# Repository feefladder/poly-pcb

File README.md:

# Johnson solid lamps!

So I thought it'd be superduper cool to make lamps as like johnson solids, so here's some kicad files for that.

There's two versions for each polygon:
1. solder mask only.
2. Solder mask and edge cuts

So you can create directional lamps with soft light in the facing direction using the pcb as diffuser adn stronger light in the backfacing direction.

More will be added once a lamp is actually made

## Exporting for jlpcb

Great thanks to [FunDeckHermit's](https://github.com/FunDeckHermit/NURD-Template) pcb exporter. I've slightly modified it so I can run it from the top-level on any file.

upload zip file to jlpcb. It can be that edge cuts don't work. fix in inkscape.

## Making mask and edge cuts

mask:

1. Plot svgs. Set F.Cu, B.Cu to all layers
2. open F.Cu in inkscape
3. select all, 2x`Ctrl-Shift-G`, `Ctrl-Shift-C`, `Ctrl-Alt-C`, `Ctrl-Shift-+` `Ctrl-Shift-)`
4. There will be some specs, either:
   - have a great time with the node tool
   - `Ctrl-Shift-K` to unmerge, select desired polygons, `!` to invert selection and delete
4. save as...
5. in kicad, `Ctrl-Shift-L`, enable "place at position `0,0`

edge:

1. Plot svgs. Set F.Cu, B.Cu, Edge.Cuts to all layers
2. open F.Cu in inkscape
3. select all, 2x`Ctrl-Shift-G`, `Ctrl-Shift-C`, `Ctrl-Alt-C`, `Ctrl-Shift-+` 2x`Ctrl-Shift-)`
4. There will be specs and some tiny gaps/overlaps.
   - fixs specs as before
   - overlaps can be fixed with running `Ctrl-Shift-+`
   - tiny gaps are equally bad. These require some fun with the node tool
     1. `Shift-doubleclick` at the narrowest point to place nodes
     2. split
     3. overlapping nodes: box select one, shift-click to get the bottom, then select the other, connect with edge, then merge to one
4. save as...
5. in kicad, `Ctrl-Shift-L`, enable "place at position `0,0`

# Reflections after making 3 lamps and soldering 350+ LEDs

So yeah, I think I'll really order the next pcbs with the leds assembled

Bending the header pins with a pcb works, but the led next to the header may want a bit of lovd afterwards. I think the flexing causes microfractures or something, but in any case, the leds stop there

## overview

1. Sphenocorona - some leds not working because of flexing breaking solder joints. Somehow it makes noise?
2. Thawro - perfect! I removed-and-bypassed some leds because I thought they were broken, but turned out it was because of WLED shenanigans
3. Bilb - smooth rolling

## WLED shenanigans

So whenever you set a pattern at boot, the length of the strip is saved in the json at "stop", so whenever increasing strip length, the leds after will not show.

Still not sure which is the best pattern for debugging leds. Solid deffo not, it needs to be changing, because a led that got a "be pink" signal will stay pink without further input. Android is fine, but when the strip setting is much larger, it is not happy. Ideally it'd be some sort of "two-color-twinkle" or something.

## howto header pins

general policy: Every bare edge exposes headers. Use a triangle full pcb to bend them in place. You want to bend it so the pcb can be flatter than it needs to be, otherwise angled pins make inserting a headache (especially for later boards).

## sharp angles

Sharp dihedral angles make the corner leds collide, resulting in a slightly sad shape. maybe add tiny jumper pads to easily bypass a led.

## Control board

Ah yes, so the ESP32-C3-WROOM boards start up in a boot loop. To solve, you have to hold BOOT (GPIO9, next to GND) low and tap EN, as this person on Github said. GPIO9 can be set as "cycle presets" or something, because getting your phone out all the time is sad.

## Double-size?

So these lamps are like nice for in a bedroom or toilet, but for living room, make double-size pcbs with two connections so they are also compatible with the others

## blrubs

ah yes ws2812s dont like fighting data, so need to cut some data pins to avoid that.

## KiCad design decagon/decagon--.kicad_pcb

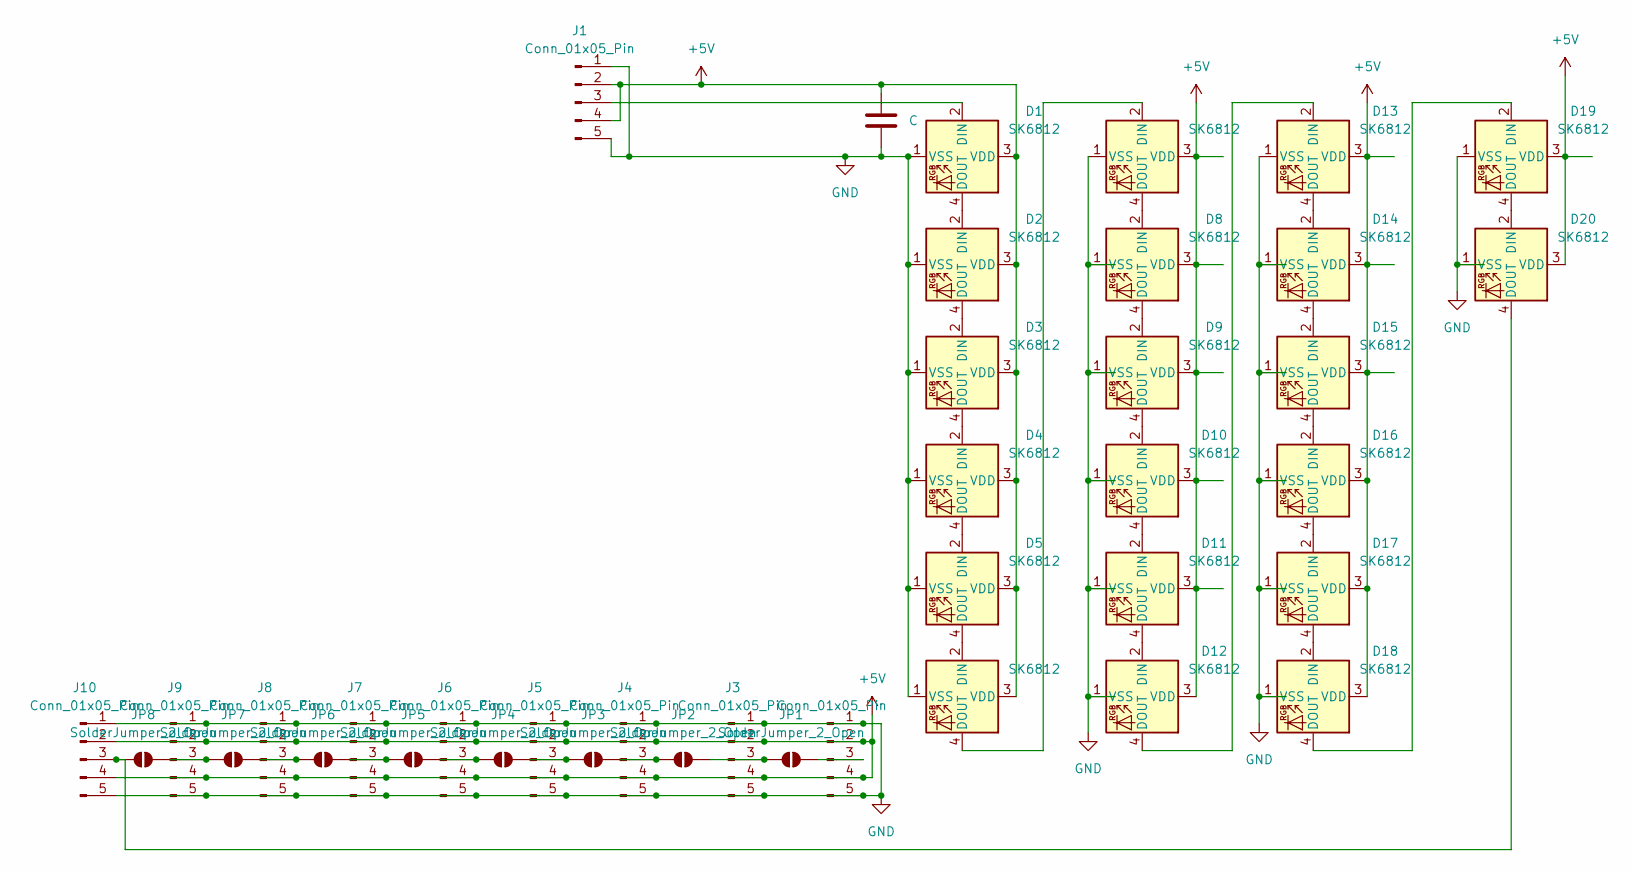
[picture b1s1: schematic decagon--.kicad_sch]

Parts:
C1: C; C_0805_2012Metric_Pad1.18x1.45mm_HandSolder
D1, D2, D3, D4, D5, D6, D7, D8, D9, D10, D11, D12, D13, D14, D15, D16, D17, D18, D19, D20: SK6812; LED_SK6812_PLCC4_5.0x5.0mm_P3.2mm
J1, J2, J3, J4, J5, J6, J7, J8, J9, J10: Conn_01x05_Pin; PinHeader_1x05_P2.54mm_Vertical
JP1, JP2, JP3, JP4, JP5, JP6, JP7, JP8: SolderJumper_2_Open; SolderJumper-2_P1.3mm_Open_RoundedPad1.0x1.5mm

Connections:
+5V: C1.2, D1.3 (VDD), D2.3 (VDD), D3.3 (VDD), D4.3 (VDD), D5.3 (VDD), D6.3 (VDD), D7.3 (VDD), D8.3 (VDD), D9.3 (VDD), D10.3 (VDD), D11.3 (VDD), D12.3 (VDD), D13.3 (VDD), D14.3 (VDD), D15.3 (VDD), D16.3 (VDD), D17.3 (VDD), D18.3 (VDD), D19.3 (VDD), D20.3 (VDD), J1.2, J1.4, J2.2, J2.4, J3.2, J3.4, J4.2, J4.4, J5.2, J5.4, J6.2, J6.4, J7.2, J7.4, J8.2, J8.4, J9.2, J9.4, J10.2, J10.4
GND: C1.1, D1.1 (VSS), D2.1 (VSS), D3.1 (VSS), D4.1 (VSS), D5.1 (VSS), D6.1 (VSS), D7.1 (VSS), D8.1 (VSS), D9.1 (VSS), D10.1 (VSS), D11.1 (VSS), D12.1 (VSS), D13.1 (VSS), D14.1 (VSS), D15.1 (VSS), D16.1 (VSS), D17.1 (VSS), D18.1 (VSS), D19.1 (VSS), D20.1 (VSS), J1.1, J1.5, J2.1, J2.5, J3.1, J3.5, J4.1, J4.5, J5.1, J5.5, J6.1, J6.5, J7.1, J7.5, J8.1, J8.5, J9.1, J9.5, J10.1, J10.5
unnamed: D1.2 (DIN), J1.3
unnamed: D1.4 (DOUT), D2.2 (DIN)
unnamed: D2.4 (DOUT), D3.2 (DIN)
unnamed: D3.4 (DOUT), D4.2 (DIN)
unnamed: D4.4 (DOUT), D5.2 (DIN)
unnamed: D5.4 (DOUT), D6.2 (DIN)
unnamed: D6.4 (DOUT), D7.2 (DIN)
unnamed: D7.4 (DOUT), D8.2 (DIN)
unnamed: D8.4 (DOUT), D9.2 (DIN)
unnamed: D9.4 (DOUT), D10.2 (DIN)
unnamed: D10.4 (DOUT), D11.2 (DIN)
unnamed: D11.4 (DOUT), D12.2 (DIN)
unnamed: D12.4 (DOUT), D13.2 (DIN)
unnamed: D13.4 (DOUT), D14.2 (DIN)
unnamed: D14.4 (DOUT), D15.2 (DIN)
unnamed: D15.4 (DOUT), D16.2 (DIN)
unnamed: D16.4 (DOUT), D17.2 (DIN)
unnamed: D17.4 (DOUT), D18.2 (DIN)
unnamed: D18.4 (DOUT), D19.2 (DIN)
unnamed: D19.4 (DOUT), D20.2 (DIN)
unnamed: D20.4 (DOUT), J10.3, JP8.1 (A)
unnamed: J2.3, JP1.2 (B)
unnamed: J3.3, JP1.1 (A), JP2.2 (B)
unnamed: J4.3, JP2.1 (A), JP3.2 (B)
unnamed: J5.3, JP3.1 (A), JP4.2 (B)
unnamed: J6.3, JP4.1 (A), JP5.2 (B)
unnamed: J7.3, JP5.1 (A), JP6.2 (B)
unnamed: J8.3, JP6.1 (A), JP7.2 (B)
unnamed: J9.3, JP7.1 (A), JP8.2 (B)

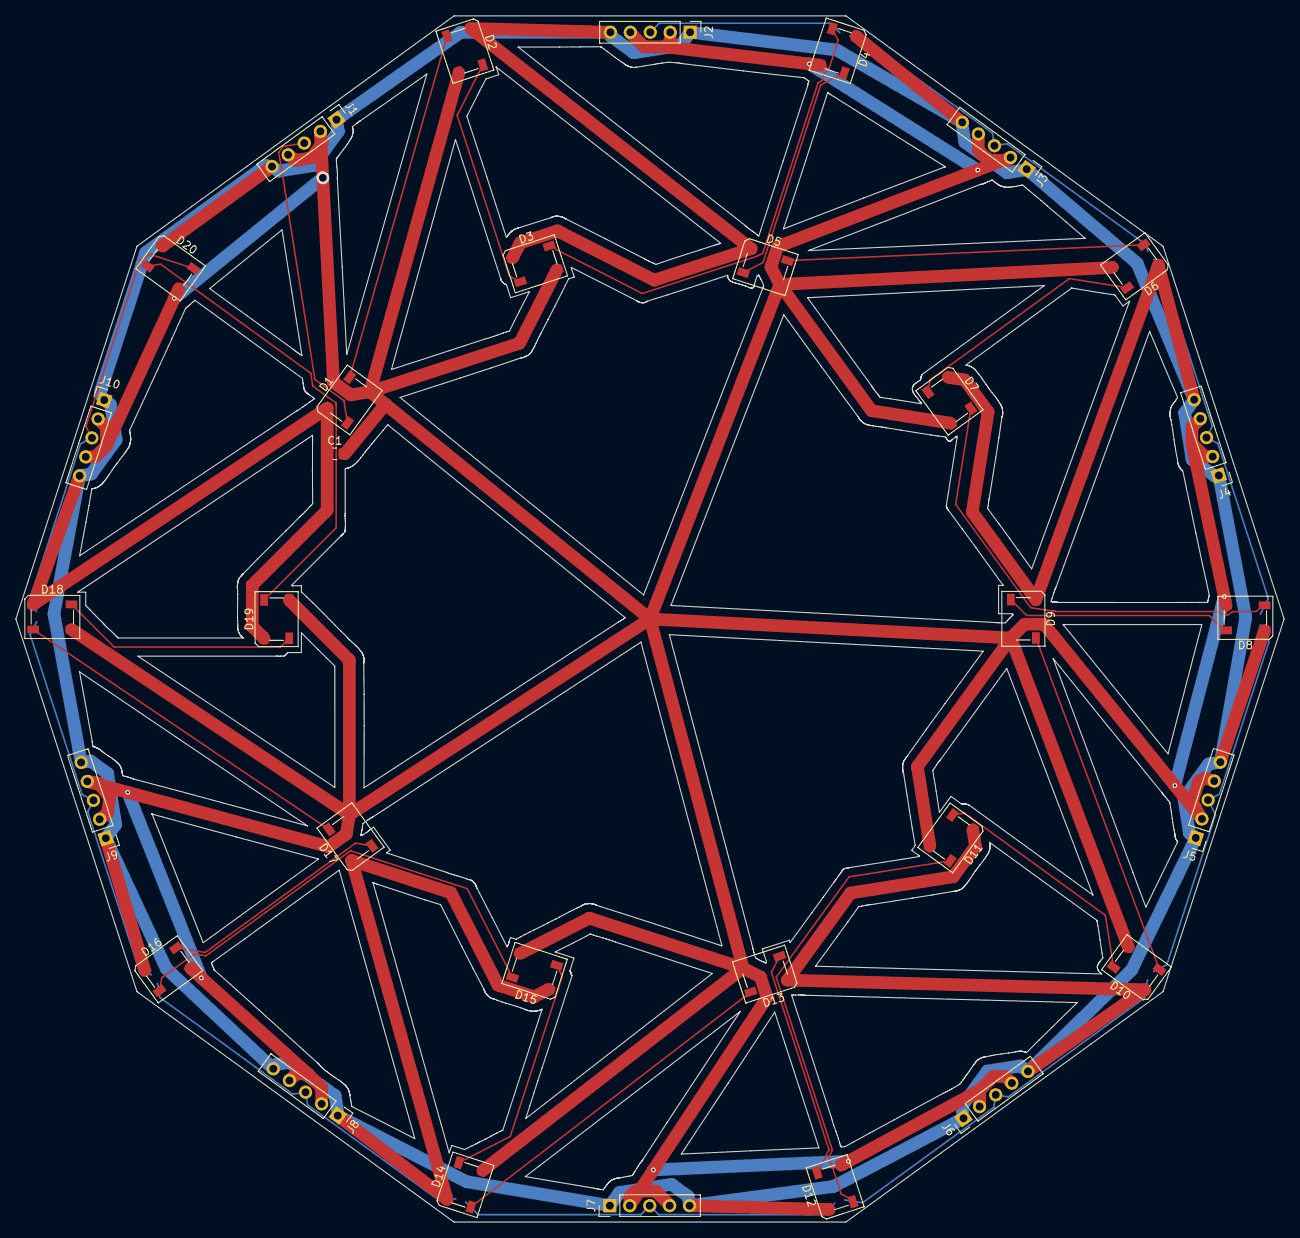
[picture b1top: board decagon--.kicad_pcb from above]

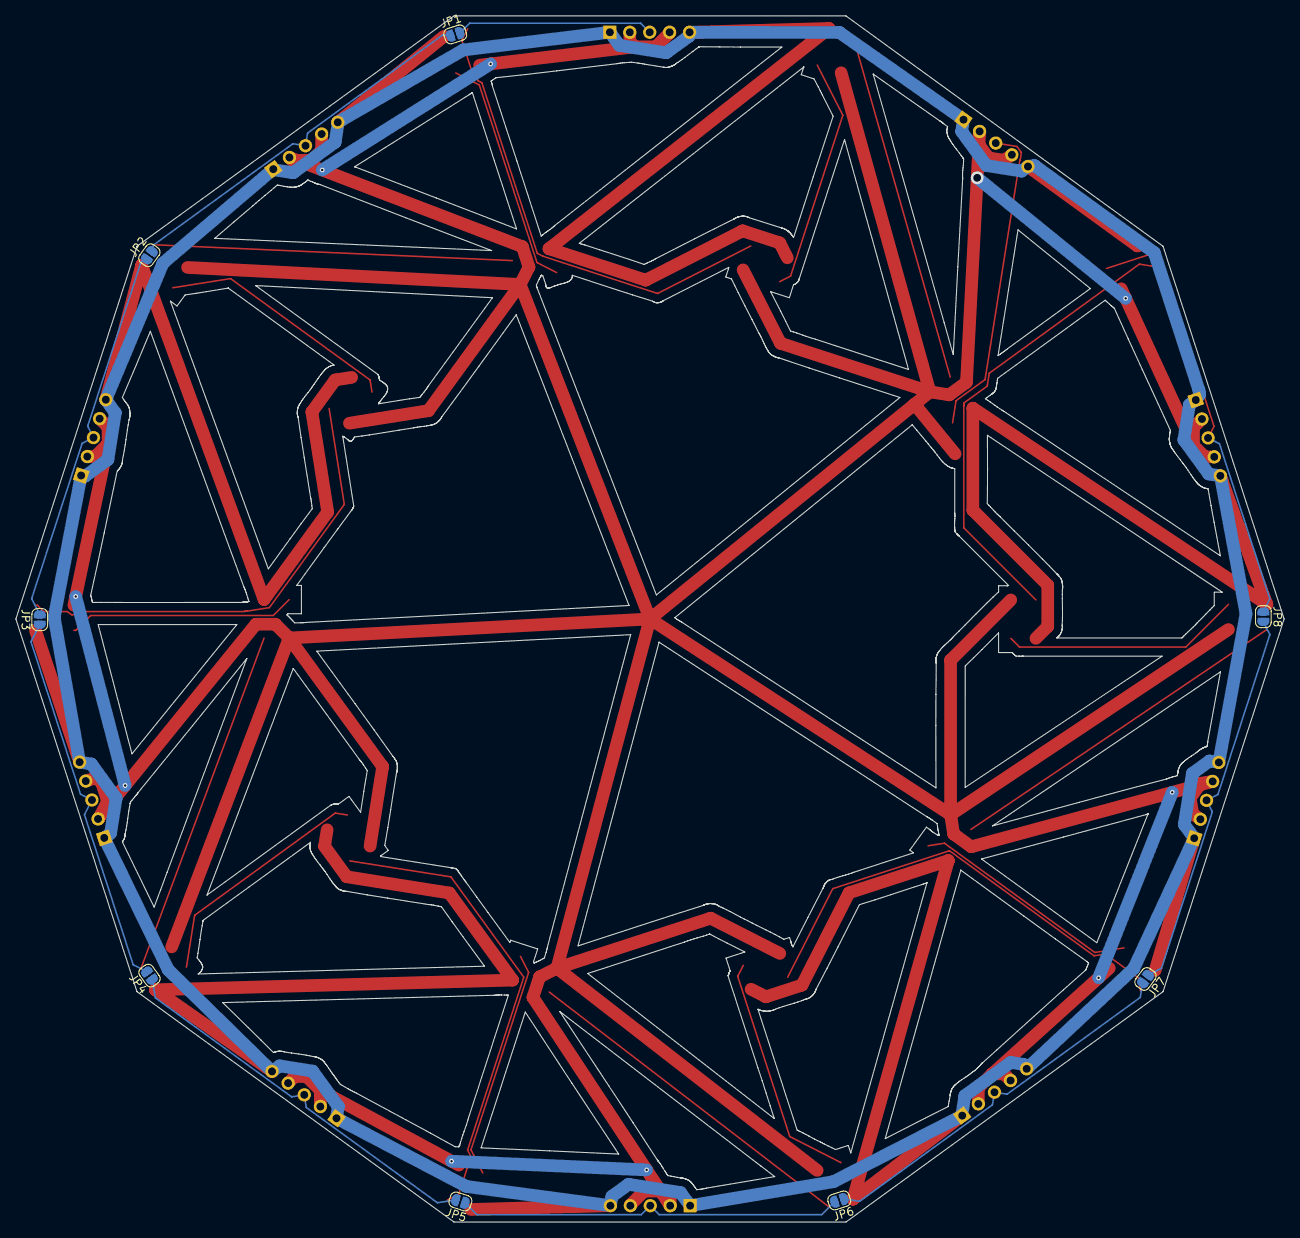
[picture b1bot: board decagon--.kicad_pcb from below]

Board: 2 copper layers, 161.7 x 153.8 mm, 39 parts (8 on the bottom side), 31 nets.

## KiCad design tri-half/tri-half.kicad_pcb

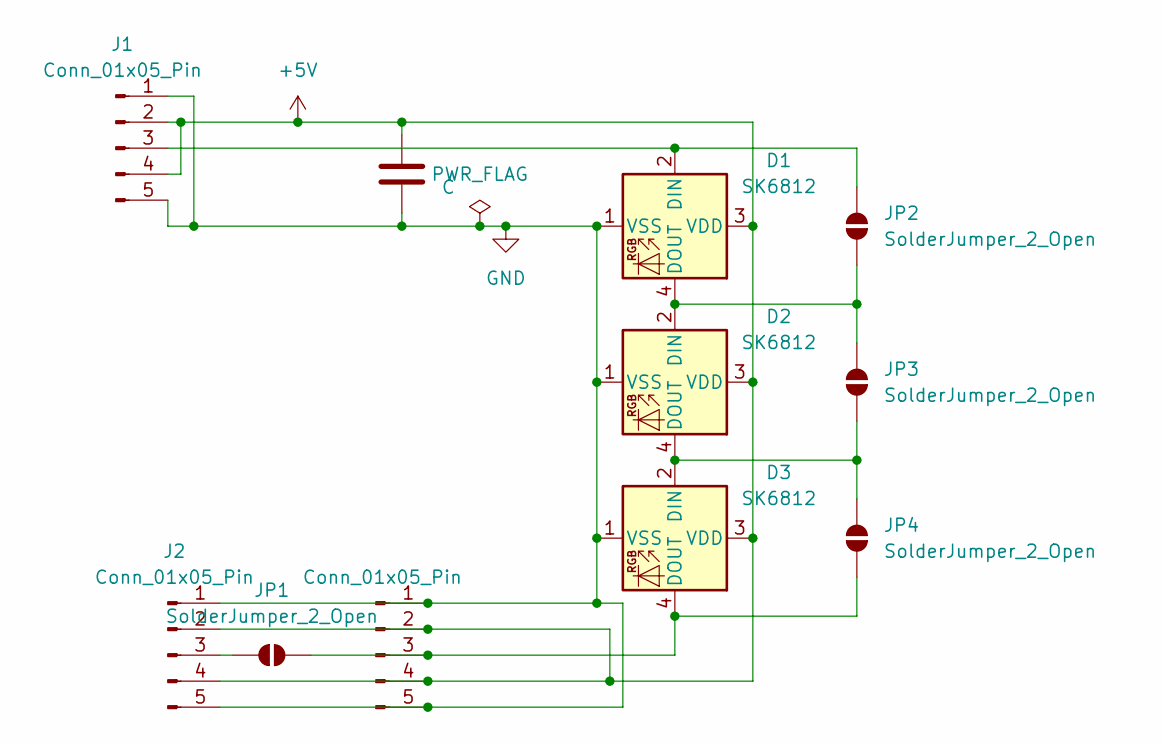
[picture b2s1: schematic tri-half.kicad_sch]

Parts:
C1: C; C_0805_2012Metric_Pad1.18x1.45mm_HandSolder
D1, D2, D3: SK6812; LED_SK6812_PLCC4_5.0x5.0mm_P3.2mm
J1, J2, J3: Conn_01x05_Pin; PinHeader_1x05_P2.54mm_Vertical
JP1: SolderJumper_2_Open; SolderJumper-2_P1.3mm_Open_Pad1.0x1.5mm
JP2, JP3, JP4: SolderJumper_2_Open; SolderJumper-2_P1.3mm_Open_RoundedPad1.0x1.5mm

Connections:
+5V: C1.1, D1.3 (VDD), D2.3 (VDD), D3.3 (VDD), J1.2, J1.4, J2.2, J2.4, J3.2, J3.4
GND: C1.2, D1.1 (VSS), D2.1 (VSS), D3.1 (VSS), J1.1, J1.5, J2.1, J2.5, J3.1, J3.5
unnamed: D1.2 (DIN), J1.3, JP2.2 (B)
unnamed: D1.4 (DOUT), D2.2 (DIN), JP2.1 (A), JP3.2 (B)
unnamed: D2.4 (DOUT), D3.2 (DIN), JP3.1 (A), JP4.2 (B)
unnamed: D3.4 (DOUT), J3.3, JP1.2 (B), JP4.1 (A)
unnamed: J2.3, JP1.1 (A)

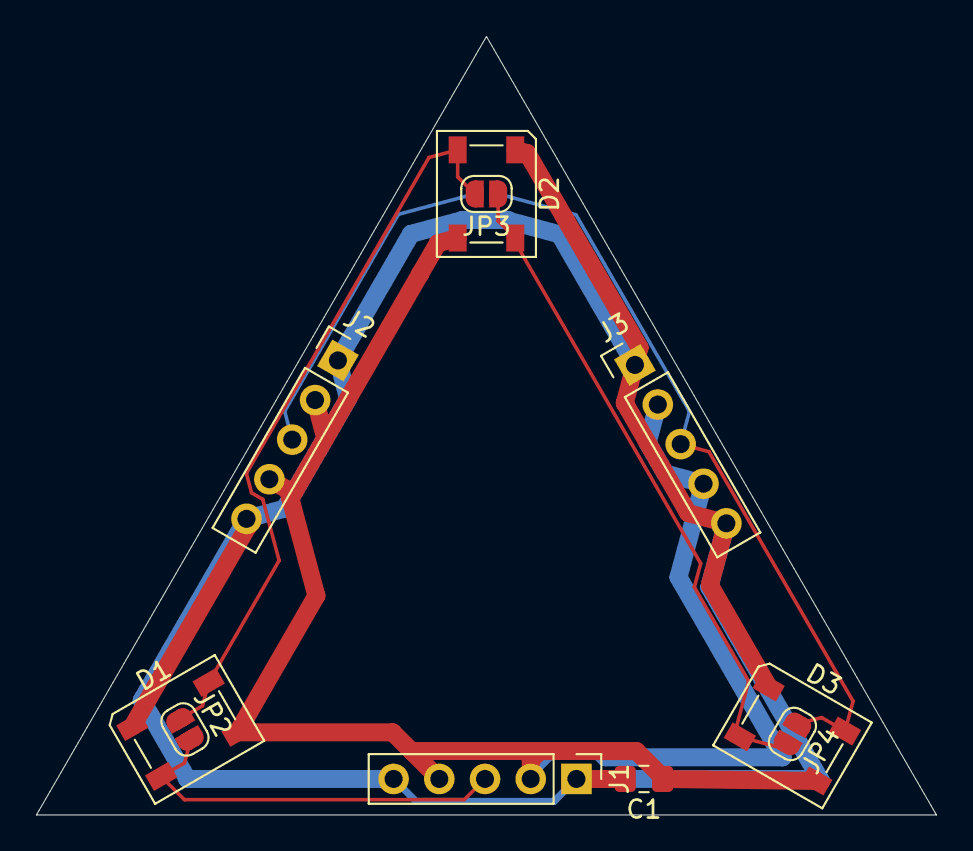
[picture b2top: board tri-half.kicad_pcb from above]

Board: 2 copper layers, 50.0 x 43.3 mm, 11 parts (1 on the bottom side), 7 nets.

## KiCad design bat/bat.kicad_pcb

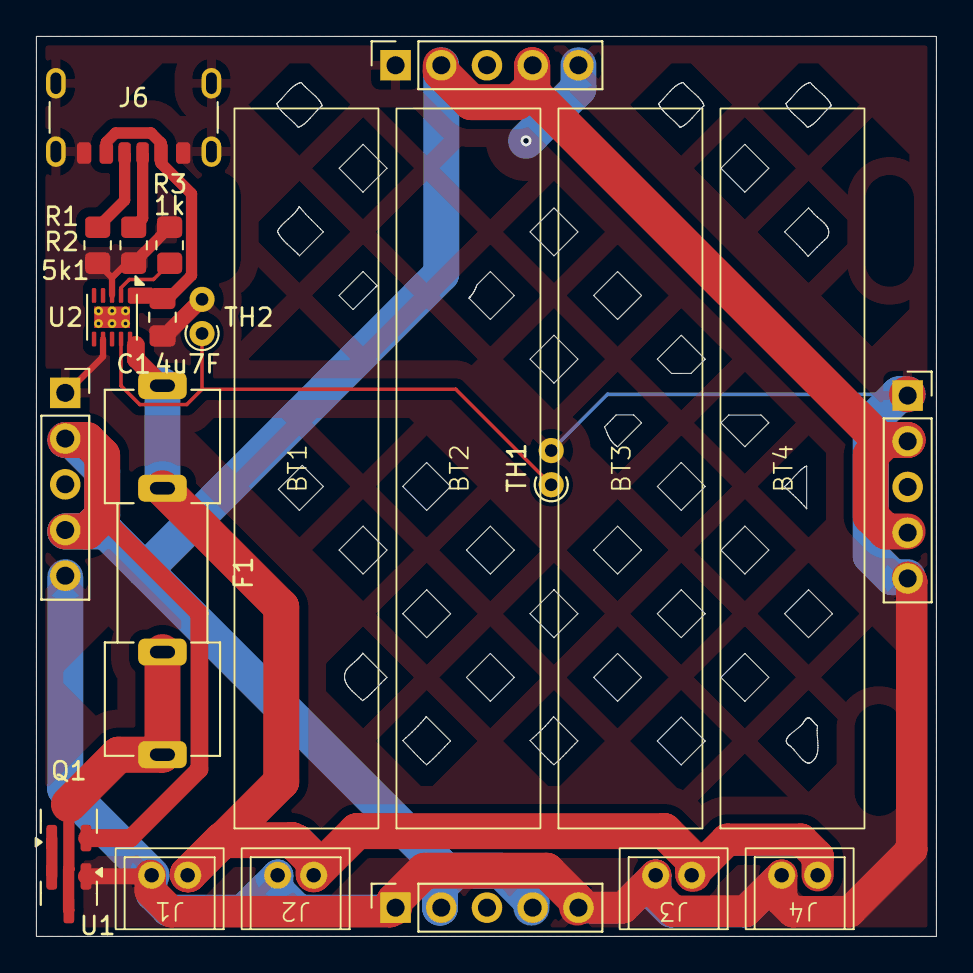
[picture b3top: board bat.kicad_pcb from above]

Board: 2 copper layers, 50.0 x 50.0 mm, 23 parts (0 on the bottom side), 10 nets.

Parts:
BT1, BT2, BT3, BT4: Battery_Cell; battery_802540_sideways
C1: 4u7F; C_0805_2012Metric_Pad1.18x1.45mm_HandSolder
F1: Fuse_Small; fuseholder
J1, J2, J3, J4: Conn_01x02_Pin; PH2.0
J6: USB_C_Receptacle_PowerOnly_6P; USB_C_Receptacle_GCT_USB4125-xx-x-0190_6P_TopMnt_Horizontal
J7, J8, J9, J10: Conn_01x05_Socket; PinSocket_1x05_P2.54mm_Vertical
Q1: BC02P28TA; SOT-23
R1, R2: 5k1; R_0805_2012Metric_Pad1.20x1.40mm_HandSolder
R3: 1k; R_0805_2012Metric_Pad1.20x1.40mm_HandSolder
TH1, TH2: Thermistor_NTC; R_Axial_DIN0204_L3.6mm_D1.6mm_P1.90mm_Vertical
U1: MICRONE ME2801A33M3G; SOT-23
U2: BQ2404; WSON-10-1EP_2.5x2.5mm_P0.5mm_EP1.2x2mm_ThermalVias

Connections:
+BATT: F1.1, J1.1, J2.1, J3.1, J4.1, U2.10 (OUT)
GND: C1.2, J1.2, J2.2, J3.2, J4.2, J6.A12 (GND), J6.B12 (GND), J6.S1 (SHIELD), J7.1, J7.5, J8.1, J8.5, J9.1, J9.5, J10.1, J10.5, R1.1, R2.2, R3.2, TH1.2, TH2.2, U1.1 (GND), U2.3 (VSS), U2.7 (ISET2)
unnamed: J6.A5 (CC1), R1.2
unnamed: J6.B5 (CC2), R2.1
unnamed: J7.2, J7.4, J8.2, J8.4, J9.2, J9.4, J10.2, J10.4, Q1.2 (S)
unnamed: F1.2, Q1.3 (D), U1.3 (VDD)
unnamed: Q1.1 (G), U1.2 (VOUT)
unnamed: R3.1, U2.2 (ISET)
unnamed: TH1.1, TH2.1, U2.9 (TS)
VBUS: C1.1, J6.A9 (VBUS), J6.B9 (VBUS), U2.1 (IN)

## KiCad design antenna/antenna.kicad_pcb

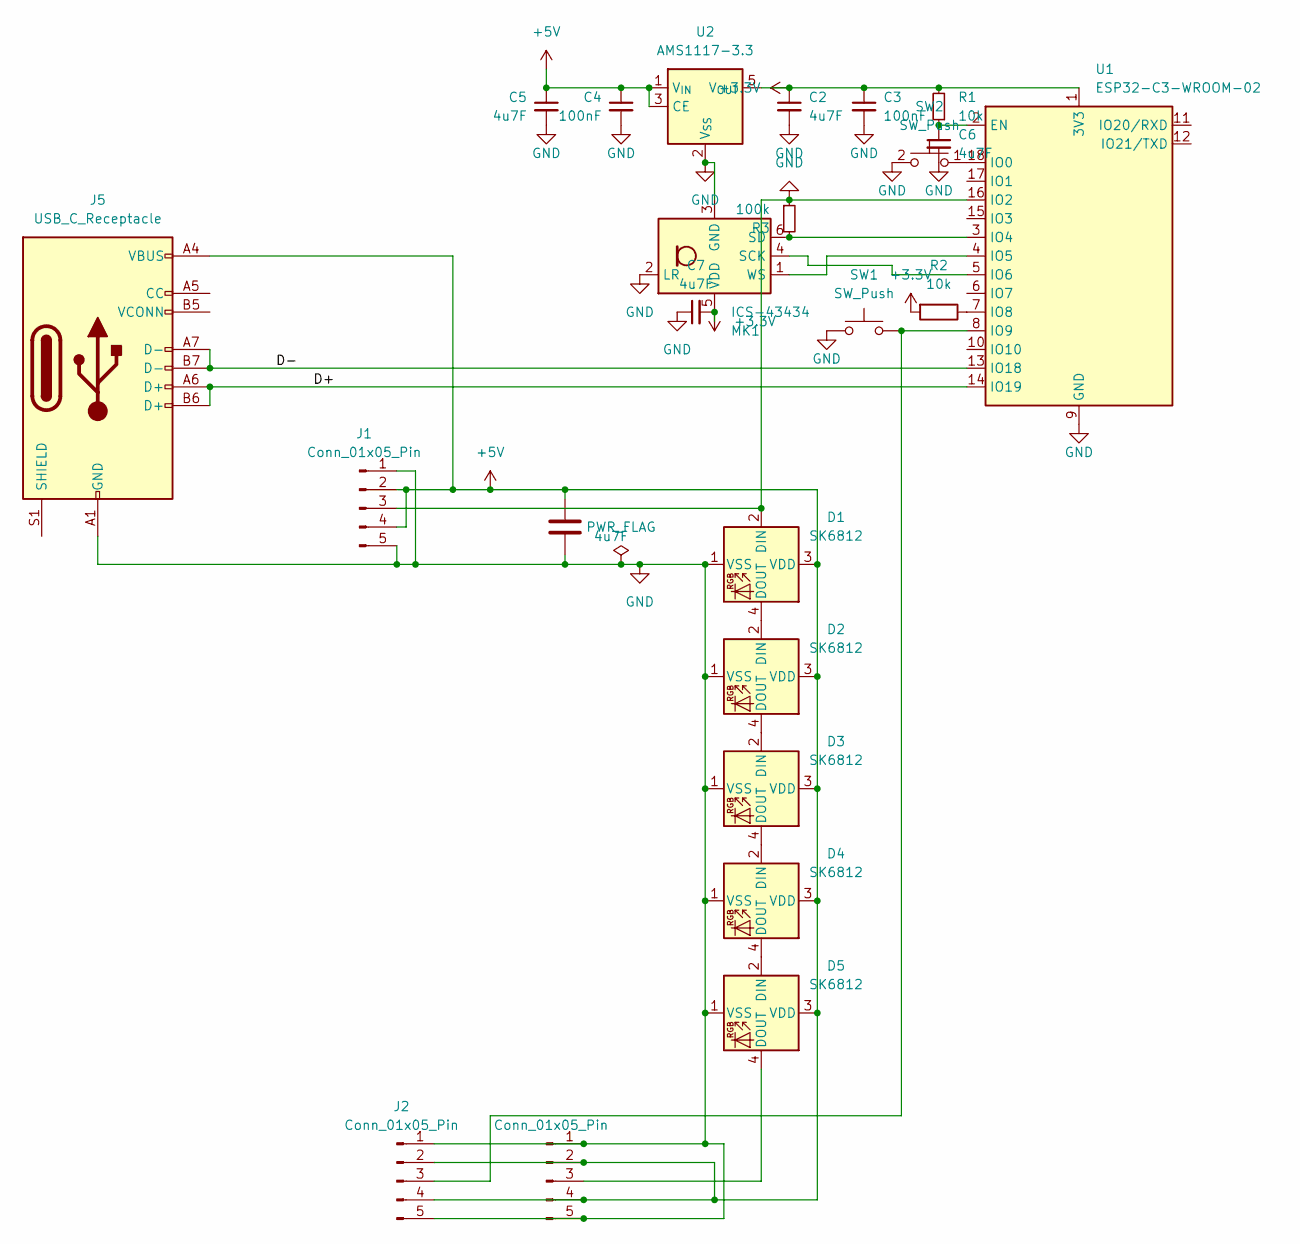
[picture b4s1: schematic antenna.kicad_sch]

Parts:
C1, C2, C5, C6, C7: 4u7F; C_0805_2012Metric_Pad1.18x1.45mm_HandSolder
C3, C4: 100nF; C_0805_2012Metric_Pad1.18x1.45mm_HandSolder
D1, D2, D3, D4, D5: SK6812; LED_SK6812_PLCC4_5.0x5.0mm_P3.2mm
J1, J2, J3: Conn_01x05_Pin; PinHeader_1x05_P2.54mm_Vertical
J5: USB_C_Receptacle; PCBTypeC_14P
MK1: ICS-43434; InvenSense_ICS-43434-6_3.5x2.65mm
R1, R2: 10k; R_0805_2012Metric_Pad1.20x1.40mm_HandSolder
R3: 100k; R_0805_2012Metric_Pad1.20x1.40mm_HandSolder
SW1: SW_Push; SW_PUSH-12mm_Wuerth-430456085736
SW2: SW_Push; SW_Tactile_SPST_NO_Straight_CK_PTS636Sx25SMTRLFS
U1: ESP32-C3-WROOM-02
U2: AMS1117-3.3; SOT-23-5

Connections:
+3.3V: C2.1, C3.1, C7.2, MK1.5 (VDD), R1.2, R2.2, U1.1 (3V3), U2.5 (V_{OUT})
+5V: C1.1, C4.1, C5.1, D1.3 (VDD), D2.3 (VDD), D3.3 (VDD), D4.3 (VDD), D5.3 (VDD), J1.2, J1.4, J2.2, J2.4, J3.2, J3.4, J5.A4 (VBUS), J5.A9 (VBUS), J5.B4 (VBUS), J5.B9 (VBUS), U2.1 (V_{IN}), U2.3 (CE)
/D+: J5.A6 (D+), J5.B6 (D+), U1.14 (IO19)
/D-: J5.A7 (D-), J5.B7 (D-), U1.13 (IO18)
GND: C1.2, C2.2, C3.2, C4.2, C5.2, C6.2, C7.1, D1.1 (VSS), D1.2 (DIN), D2.1 (VSS), D3.1 (VSS), D4.1 (VSS), D5.1 (VSS), J1.1, J1.3, J1.5, J2.1, J2.5, J3.1, J3.5, J5.A1 (GND), J5.A12 (GND), J5.B1 (GND), J5.B12 (GND), MK1.2 (LR), MK1.3 (GND), R3.1, SW1.1, SW2.2, U1.9 (GND), U1.16 (IO2), U1.19 (GND), U2.2 (V_{SS})
unnamed: D1.4 (DOUT), D2.2 (DIN)
unnamed: D2.4 (DOUT), D3.2 (DIN)
unnamed: D3.4 (DOUT), D4.2 (DIN)
unnamed: D4.4 (DOUT), D5.2 (DIN)
unnamed: D5.4 (DOUT), J3.3
unnamed: J2.3, SW1.2, U1.8 (IO9)
unnamed: MK1.4 (SCK), U1.5 (IO6)
unnamed: MK1.6 (SD), R3.2, U1.3 (IO4)
unnamed: MK1.1 (WS), U1.4 (IO5)
unnamed: C6.1, R1.1, U1.2 (EN)
unnamed: SW2.1, U1.18 (IO0)
unnamed: R2.1, U1.7 (IO8)

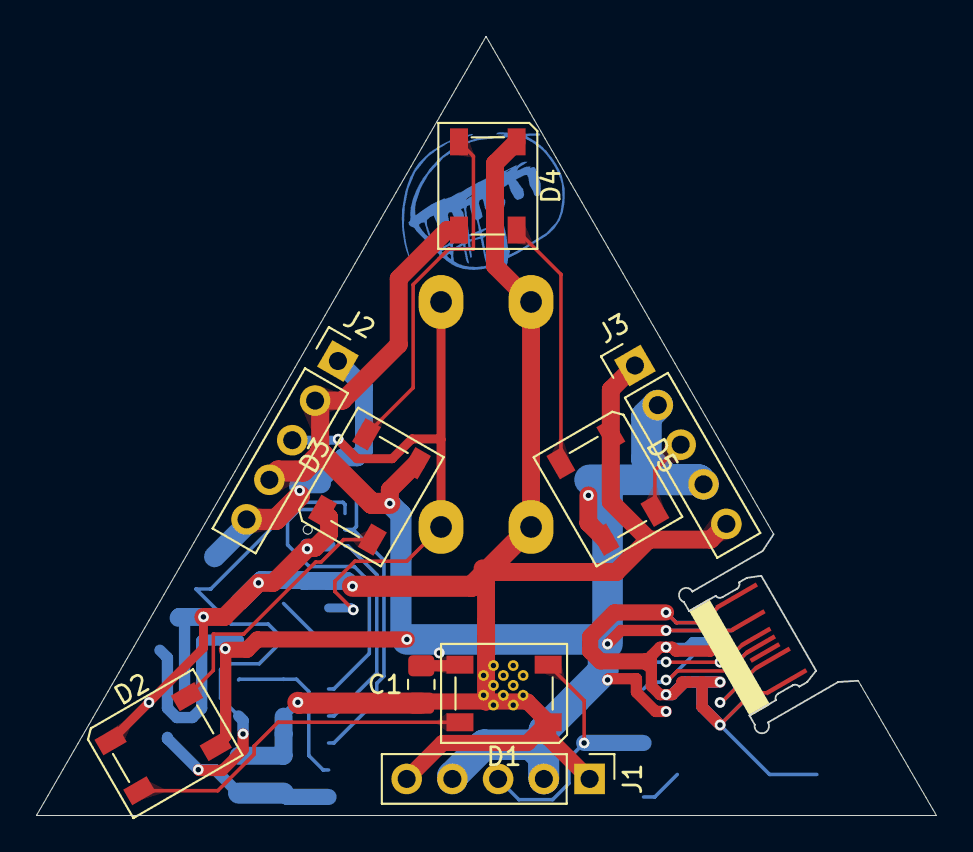
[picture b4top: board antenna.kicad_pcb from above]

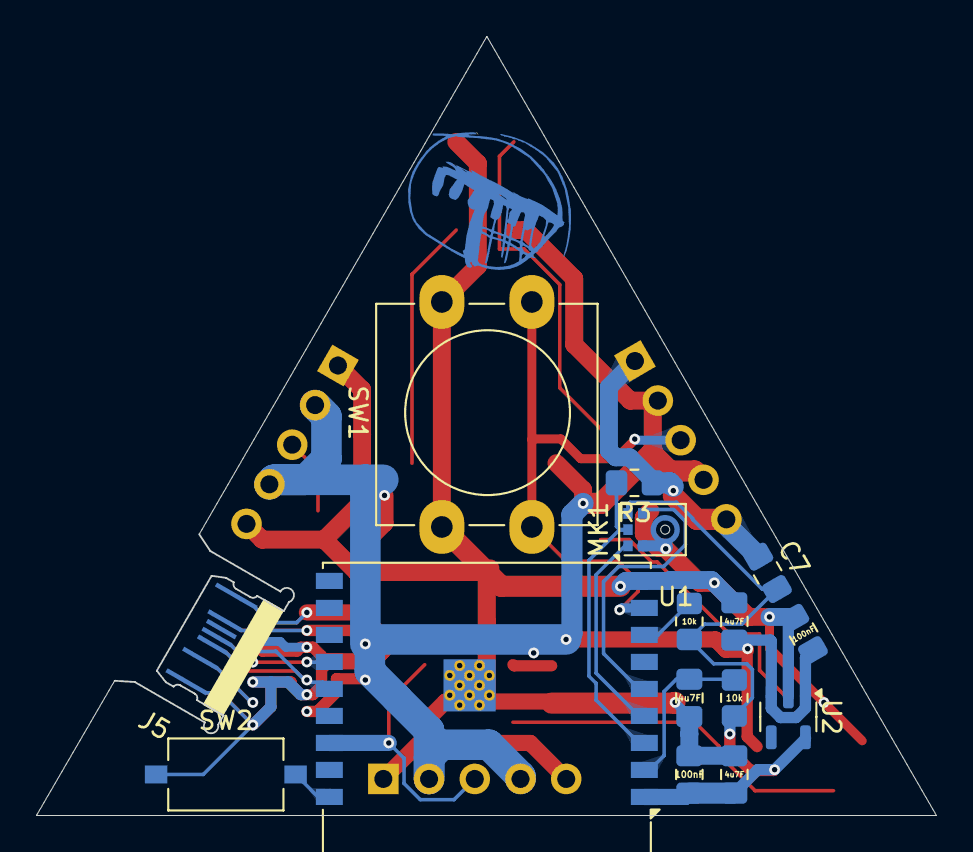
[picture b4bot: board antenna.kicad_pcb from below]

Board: 2 copper layers, 50.0 x 43.3 mm, 24 parts (15 on the bottom side), 17 nets.

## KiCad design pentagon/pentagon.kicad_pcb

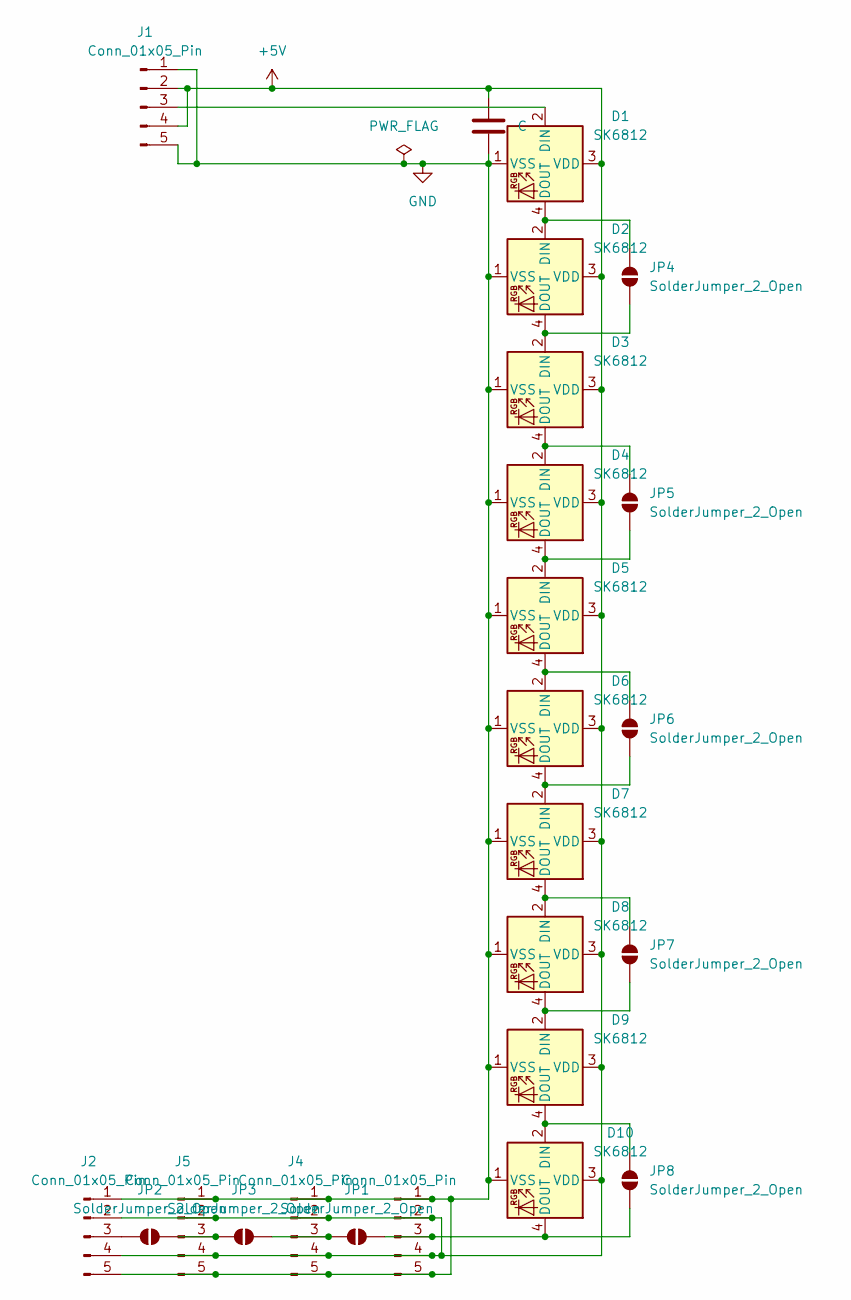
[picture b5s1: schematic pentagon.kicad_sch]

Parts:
C1: C; C_0805_2012Metric_Pad1.18x1.45mm_HandSolder
D1, D2, D3, D4, D5, D6, D7, D8, D9, D10: SK6812; LED_SK6812_PLCC4_5.0x5.0mm_P3.2mm
J1, J2, J3, J4, J5: Conn_01x05_Pin; PinHeader_1x05_P2.54mm_Vertical
JP1, JP2, JP3: SolderJumper_2_Open; SolderJumper-2_P1.3mm_Open_Pad1.0x1.5mm
JP4, JP5, JP6, JP7, JP8: SolderJumper_2_Open; SolderJumper-2_P1.3mm_Open_RoundedPad1.0x1.5mm

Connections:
+5V: C1.2, D1.3 (VDD), D2.3 (VDD), D3.3 (VDD), D4.3 (VDD), D5.3 (VDD), D6.3 (VDD), D7.3 (VDD), D8.3 (VDD), D9.3 (VDD), D10.3 (VDD), J1.2, J1.4, J2.2, J2.4, J3.2, J3.4, J4.2, J4.4, J5.2, J5.4
GND: C1.1, D1.1 (VSS), D2.1 (VSS), D3.1 (VSS), D4.1 (VSS), D5.1 (VSS), D6.1 (VSS), D7.1 (VSS), D8.1 (VSS), D9.1 (VSS), D10.1 (VSS), J1.1, J1.5, J2.1, J2.5, J3.1, J3.5, J4.1, J4.5, J5.1, J5.5
unnamed: D1.2 (DIN), J1.3
unnamed: D1.4 (DOUT), D2.2 (DIN), JP4.2 (B)
unnamed: D2.4 (DOUT), D3.2 (DIN), JP4.1 (A)
unnamed: D3.4 (DOUT), D4.2 (DIN), JP5.2 (B)
unnamed: D4.4 (DOUT), D5.2 (DIN), JP5.1 (A)
unnamed: D5.4 (DOUT), D6.2 (DIN), JP6.2 (B)
unnamed: D6.4 (DOUT), D7.2 (DIN), JP6.1 (A)
unnamed: D7.4 (DOUT), D8.2 (DIN), JP7.2 (B)
unnamed: D8.4 (DOUT), D9.2 (DIN), JP7.1 (A)
unnamed: D9.4 (DOUT), D10.2 (DIN), JP8.2 (B)
unnamed: D10.4 (DOUT), J3.3, JP1.2 (B), JP8.1 (A)
unnamed: J2.3, JP2.1 (A)
unnamed: J4.3, JP1.1 (A), JP3.2 (B)
unnamed: J5.3, JP2.2 (B), JP3.1 (A)

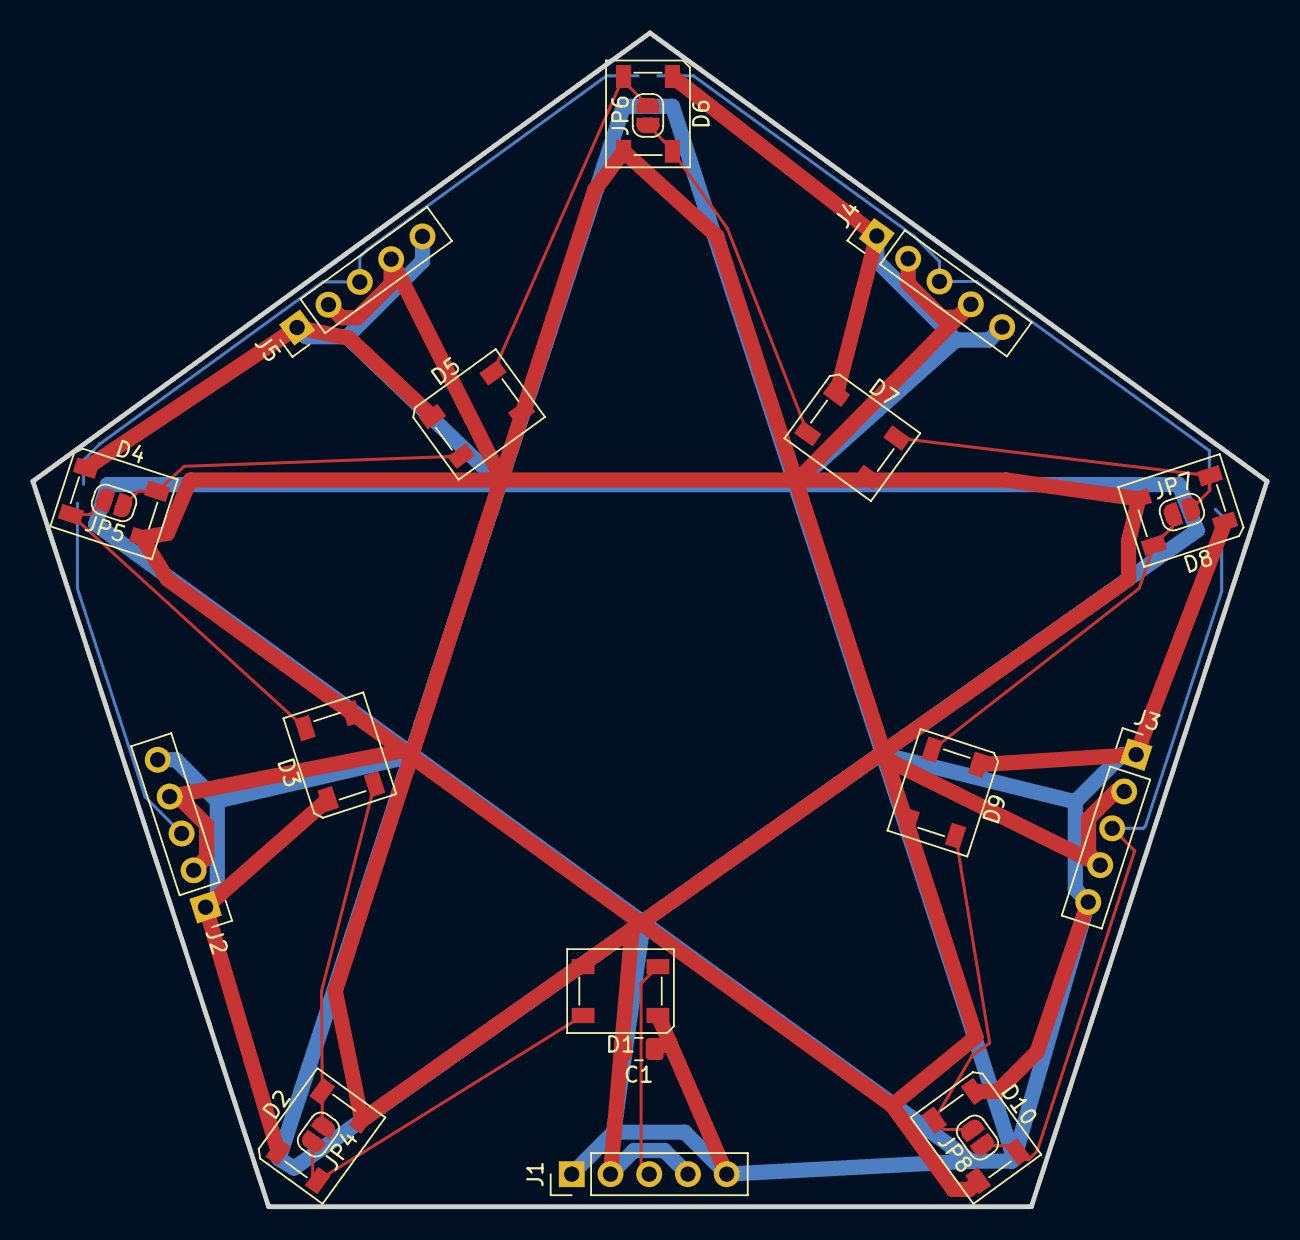
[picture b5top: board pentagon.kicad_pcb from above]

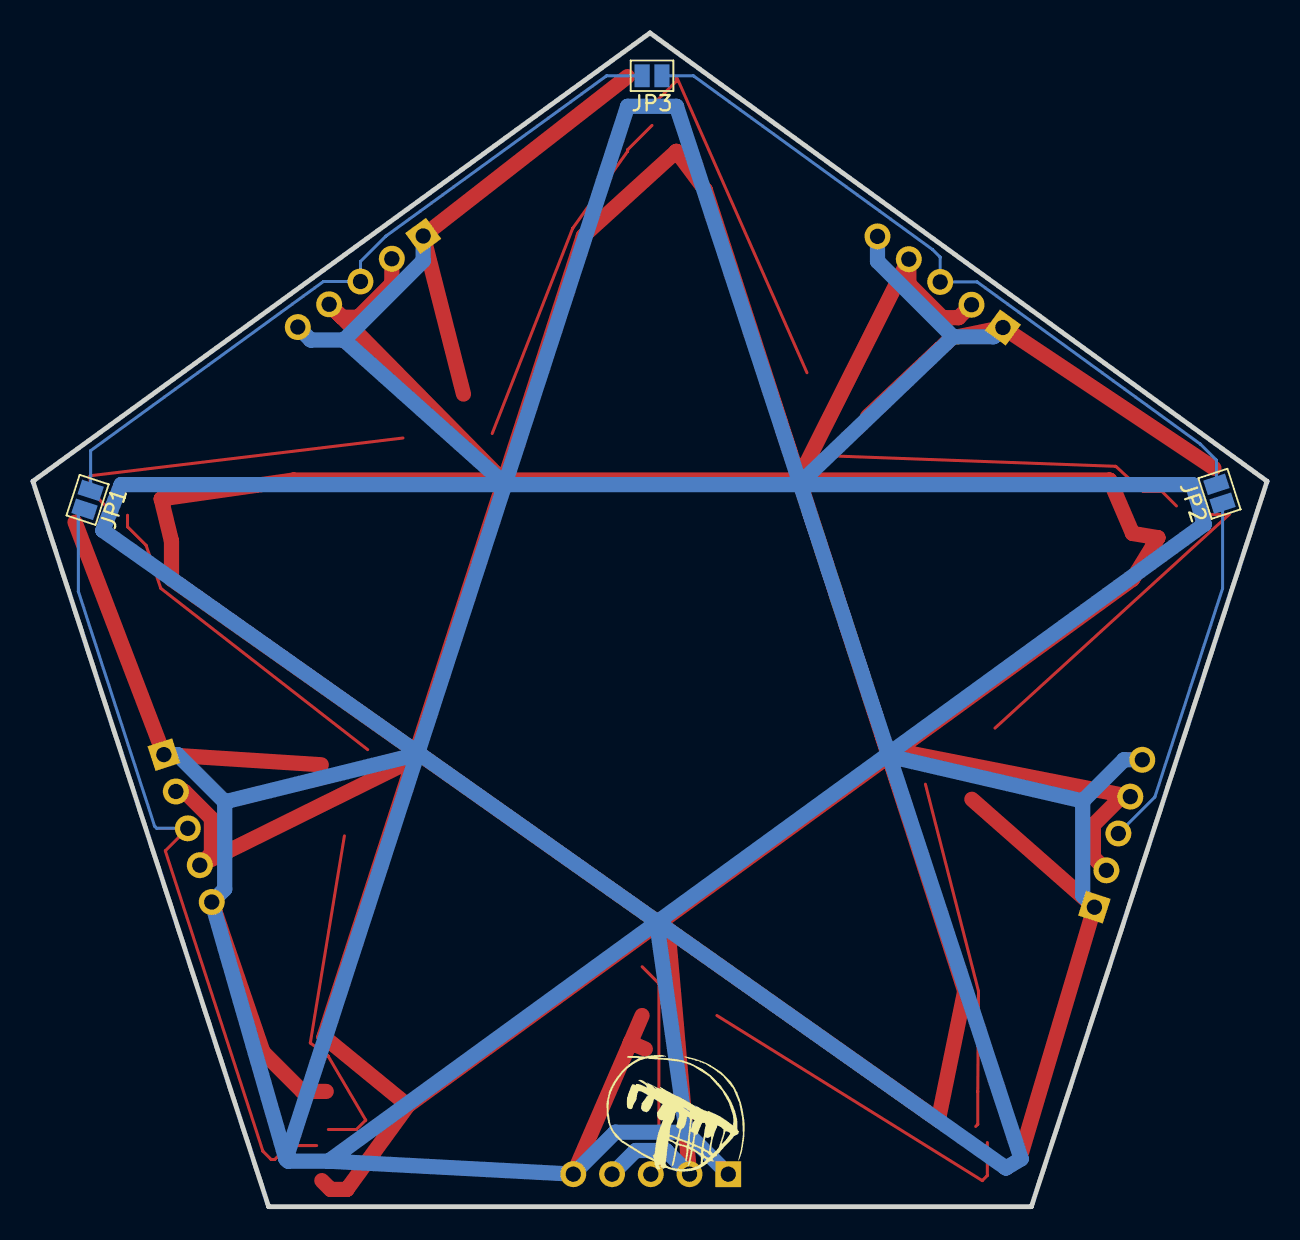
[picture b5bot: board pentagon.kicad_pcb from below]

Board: 2 copper layers, 80.9 x 76.9 mm, 24 parts (3 on the bottom side), 16 nets.

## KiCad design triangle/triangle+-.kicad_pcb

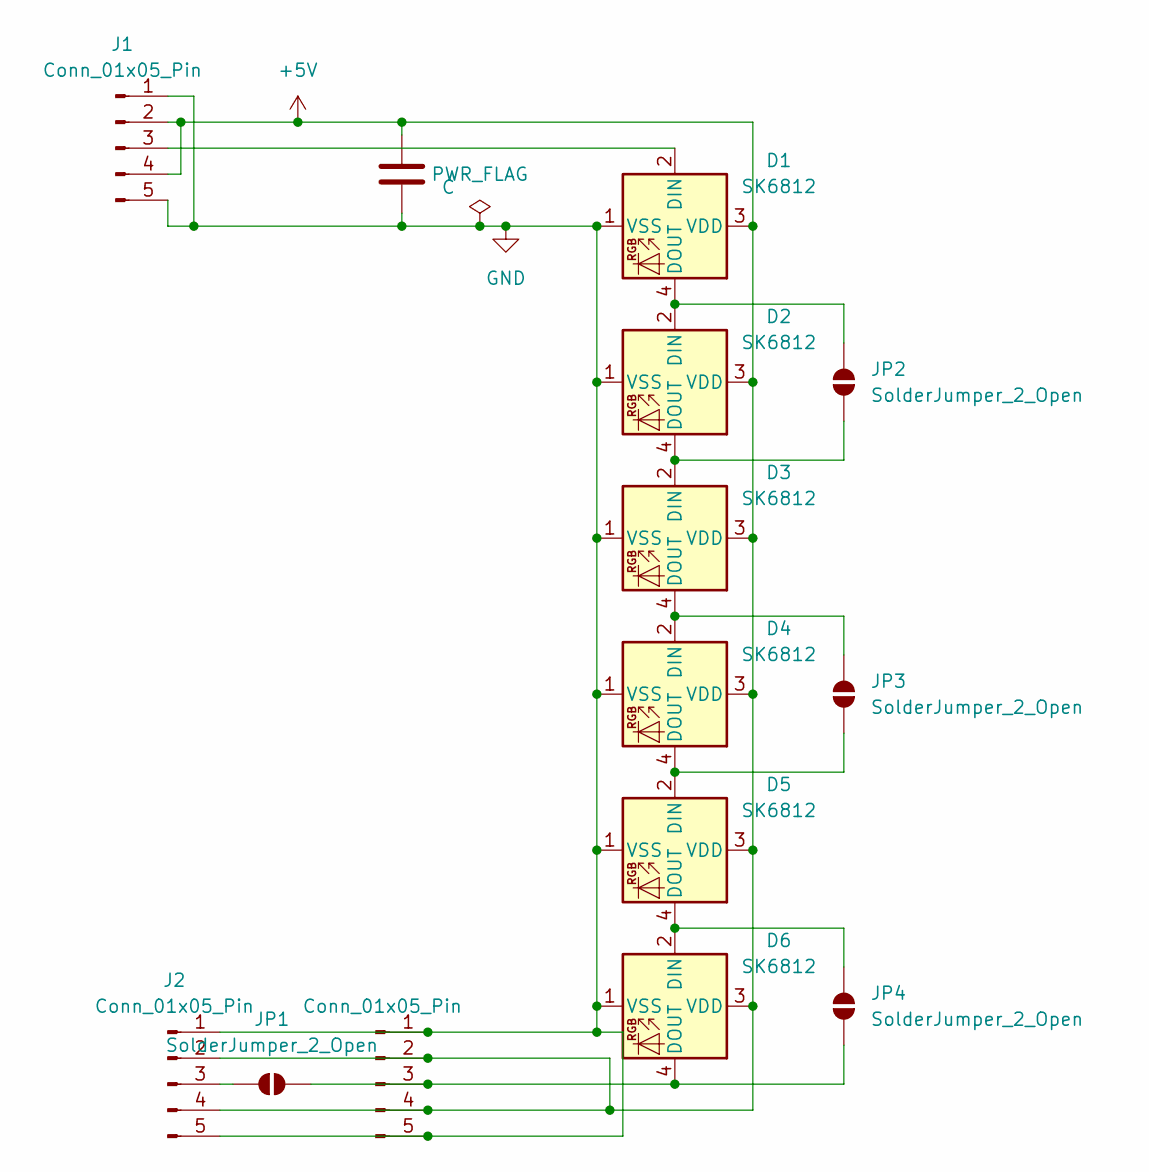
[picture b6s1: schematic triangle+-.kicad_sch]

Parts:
C1: C; C_0805_2012Metric_Pad1.18x1.45mm_HandSolder
D1, D2, D3, D4, D5, D6: SK6812; LED_SK6812_PLCC4_5.0x5.0mm_P3.2mm
J1, J2, J3: Conn_01x05_Pin; PinHeader_1x05_P2.54mm_Vertical
JP1: SolderJumper_2_Open; SolderJumper-2_P1.3mm_Open_Pad1.0x1.5mm
JP2, JP3, JP4: SolderJumper_2_Open; SolderJumper-2_P1.3mm_Open_RoundedPad1.0x1.5mm

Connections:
+5V: C1.1, D1.3 (VDD), D2.3 (VDD), D3.3 (VDD), D4.3 (VDD), D5.3 (VDD), D6.3 (VDD), J1.2, J1.4, J2.2, J2.4, J3.2, J3.4
GND: C1.2, D1.1 (VSS), D2.1 (VSS), D3.1 (VSS), D4.1 (VSS), D5.1 (VSS), D6.1 (VSS), J1.1, J1.5, J2.1, J2.5, J3.1, J3.5
unnamed: D1.2 (DIN), J1.3
unnamed: D1.4 (DOUT), D2.2 (DIN), JP2.2 (B)
unnamed: D2.4 (DOUT), D3.2 (DIN), JP2.1 (A)
unnamed: D3.4 (DOUT), D4.2 (DIN), JP3.2 (B)
unnamed: D4.4 (DOUT), D5.2 (DIN), JP3.1 (A)
unnamed: D5.4 (DOUT), D6.2 (DIN), JP4.2 (B)
unnamed: D6.4 (DOUT), J3.3, JP1.2 (B), JP4.1 (A)
unnamed: J2.3, JP1.1 (A)
